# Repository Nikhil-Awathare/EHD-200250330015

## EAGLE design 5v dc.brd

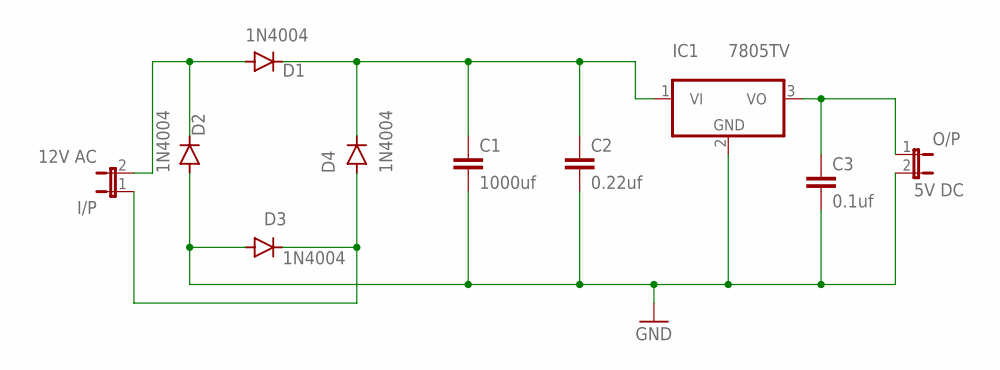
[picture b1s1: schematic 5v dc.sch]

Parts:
C1: 1000uf; C2.5-3
C2: 0.22uf; C2.5-3
C3: 0.1uf; C2.5-3
D1, D2, D3, D4: 1N4004; DO41-10
I/P: 12V AC; JP1
IC1: 7805TV; TO220V
O/P: 5V DC; JP1

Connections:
GND: C1.2, C2.2, C3.2, D2.A, D3.A, IC1.2 (GND), O/P.2
unnamed: D1.A, D2.C, I/P.2
unnamed: D3.C, D4.A, I/P.1
unnamed: C1.1, C2.1, D1.C, D4.C, IC1.1 (VI)
unnamed: C3.1, IC1.3 (VO), O/P.1

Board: 2 copper layers, 10 parts (0 on the bottom side), 5 nets, no tracks yet.
